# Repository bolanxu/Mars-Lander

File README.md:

# Mars Lander

https://youtu.be/TvxShnH4dns?si=FG6ILegN3fnswcwK

A Mars Lander control panel that simulates a landing on Mars. 
Built using simple physics, microcontrollers, and electronics.

This is is probably one of my most complex projects and it took me about a few months to build.
My first prototype was only a microcontroller development board with and 16x2 LCD screen (see /src/lcd)
And I made it in 7th grade, only about a year after I learned how to use the microcontroller.

I finish the 2nd upgraded prototype in December of 2024. I changed the LCD display to a full panel of 4 seven-segment displays, 8 leds, buttons, and potentiometers.
The code is in the /src/panel folder.

I used an microcontroller from the 8051 family, the STC125A60S2 developed by STC Microcontrollers. Compiled using SDCC.

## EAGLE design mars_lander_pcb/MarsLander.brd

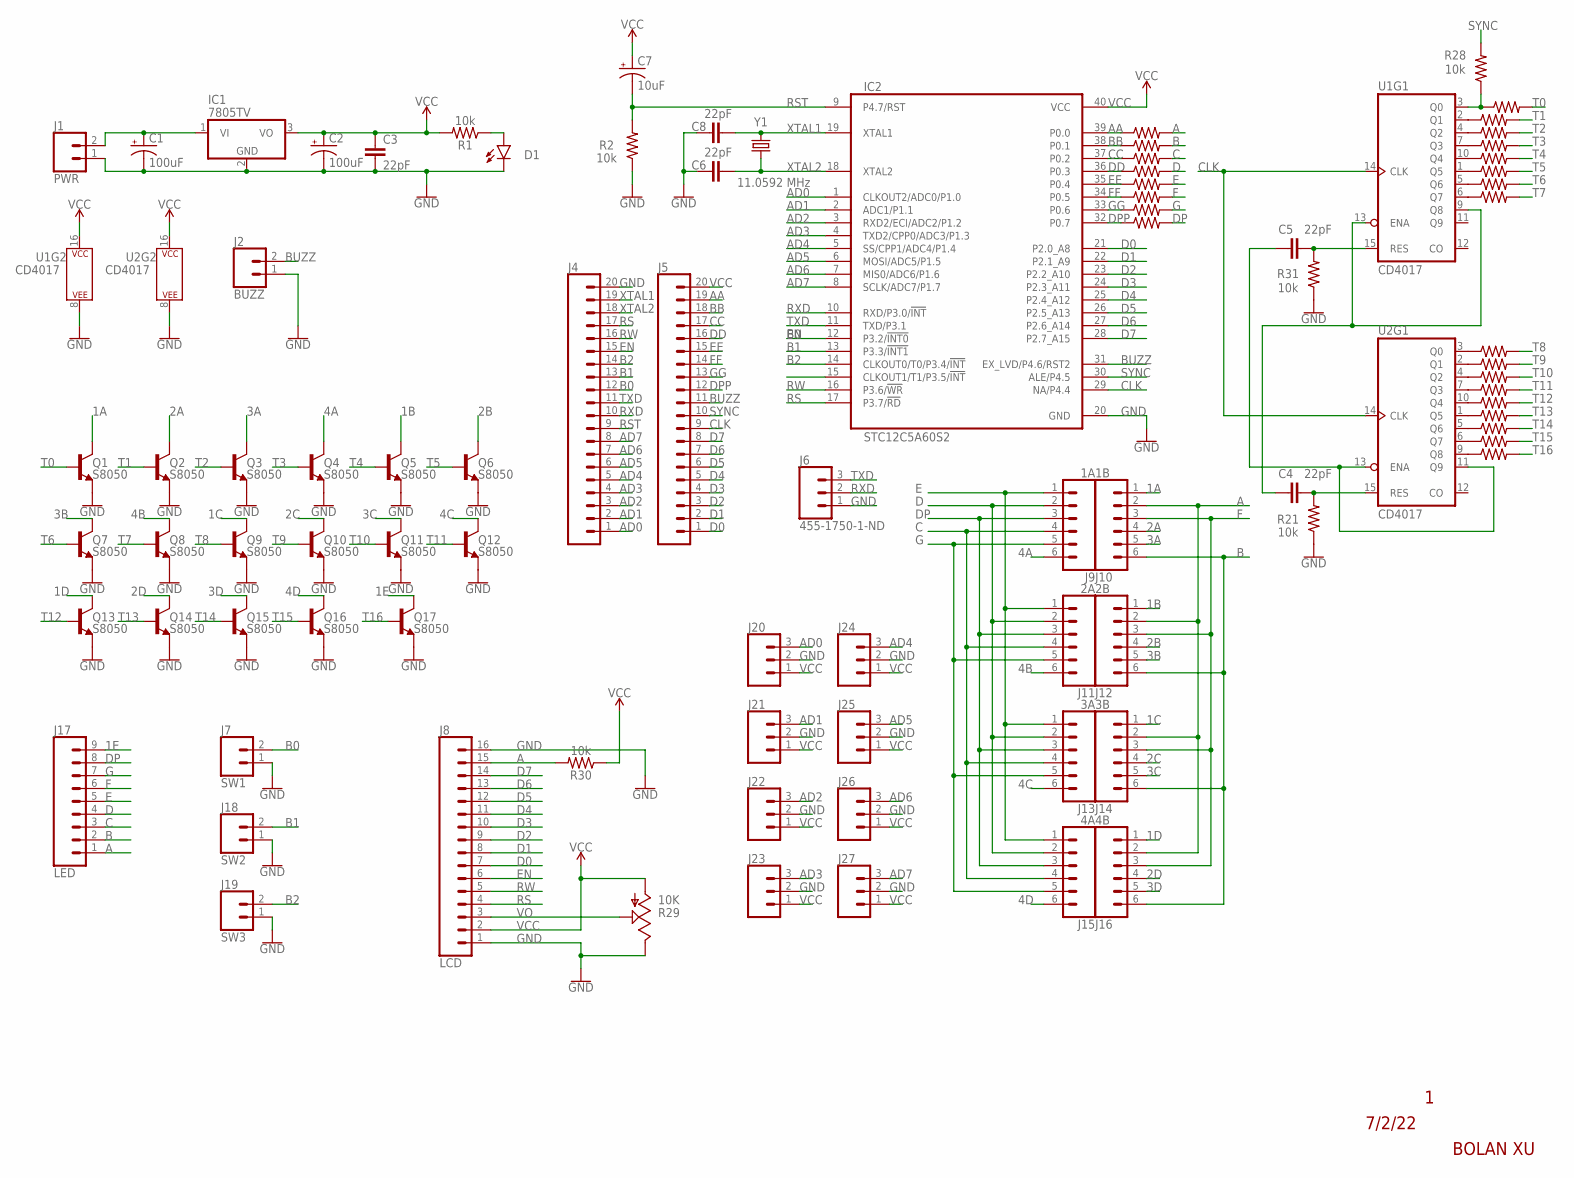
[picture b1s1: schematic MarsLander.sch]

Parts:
C1, C2: 100uF; CPOL-RADIAL-2.5MM-6.5MM
C3, C4, C5, C6, C8: 22pF; CAP-PTH-2.54
C7: 10uF; CPOL-RADIAL-2.5MM-5MM
D1: 3MM; LED_3MM
IC1: 7805TV; TO220V
IC2: STC12C5A60S2; DIL40
J1: PWR; 1X02
J2: BUZZ; 1X02
J4, J5: CONN_20; 1X20
J6, J20, J21, J22, J23, J24, J25, J26, J27: 455-1750-1-ND; 1X03
J7: SW1; 1X02
J8: LCD; 1X16
J9: 1A; 1X06
J10: 1B; 1X06
J11: 2A; 1X06
J12: 2B; 1X06
J13: 3A; 1X06
J14: 3B; 1X06
J15: 4A; 1X06
J16: 4B; 1X06
J17: LED; 1X09
J18: SW2; 1X02
J19: SW3; 1X02
Q1, Q2, Q3, Q4, Q5, Q6, Q7, Q8, Q9, Q10, Q11, Q12, Q13, Q14, Q15, Q16, Q17: S8050; TO-92
R1, R2, R3, R4, R5, R6, R7, R8, R9, R10, R11, R12, R13, R14, R15, R16, R17, R18, R19, R20, R21, R22, R23, R24, R25, R26, R27, R28, R30, R31, R33: 10k; AXIAL-0.3
R29: 10K; B25P
U1, U2: CD4017; DIP16
Y1: 11.0592 MHz; HC49U

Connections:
1A: J10.1, Q1.3 (C)
1B: J12.1, Q5.3 (C)
1C: J14.1, Q9.3 (C)
1D: J16.1, Q13.3 (C)
1E: J17.9, Q17.3 (C)
2A: J10.4, Q2.3 (C)
2B: J12.4, Q6.3 (C)
2C: J14.4, Q10.3 (C)
2D: J16.4, Q14.3 (C)
3A: J10.5, Q3.3 (C)
3B: J12.5, Q7.3 (C)
3C: J14.5, Q11.3 (C)
3D: J16.5, Q15.3 (C)
4A: J9.6, Q4.3 (C)
4B: J11.6, Q8.3 (C)
4C: J13.6, Q12.3 (C)
4D: J15.6, Q16.3 (C)
A: J8.15, J10.2, J12.2, J14.2, J16.2, J17.1, R19.P$2 (2), R30.P$2 (2)
AA: IC2.39 (P0.0), J5.19, R19.P$1 (1)
AD0: IC2.1 (CLKOUT2/ADC0/P1.0), J4.1, J20.3
AD1: IC2.2 (ADC1/P1.1), J4.2, J21.3
AD2: IC2.3 (RXD2/ECI/ADC2/P1.2), J4.3, J22.3
AD3: IC2.4 (TXD2/CPP0/ADC3/P1.3), J4.4, J23.3
AD4: IC2.5 (SS/CPP1/ADC4/P1.4), J4.5, J24.3
AD5: IC2.6 (MOSI/ADC5/P1.5), J4.6, J25.3
AD6: IC2.7 (MIS0/ADC6/P1.6), J4.7, J26.3
AD7: IC2.8 (SCLK/ADC7/P1.7), J4.8, J27.3
B: J10.6, J12.6, J14.6, J16.6, J17.2, R20.P$2 (2)
B0: IC2.12 (P3.2/!INT0), J4.12, J7.2
B1: IC2.13 (P3.3/!INT1), J4.13, J18.2
B2: IC2.14 (CLKOUT0/T0/P3.4/!INT), J4.14, J19.2
BB: IC2.38 (P0.1), J5.18, R20.P$1 (1)
BUZZ: IC2.31 (EX_LVD/P4.6/RST2), J2.2, J5.11
C: J9.4, J11.4, J13.4, J15.4, J17.3, R22.P$2 (2)
CC: IC2.37 (P0.2), J5.17, R22.P$1 (1)
CLK: IC2.29 (NA/P4.4), J5.9, U1.14 (CLK), U2.14 (CLK)
D: J9.2, J11.2, J13.2, J15.2, J17.4, R23.P$2 (2)
D0: IC2.21 (P2.0_A8), J5.1, J8.7
D1: IC2.22 (P2.1_A9), J5.2, J8.8
D2: IC2.23 (P2.2_A10), J5.3, J8.9
D3: IC2.24 (P2.3_A11), J5.4, J8.10
D4: IC2.25 (P2.4_A12), J5.5, J8.11
D5: IC2.26 (P2.5_A13), J5.6, J8.12
D6: IC2.27 (P2.6_A14), J5.7, J8.13
D7: IC2.28 (P2.7_A15), J5.8, J8.14
DD: IC2.36 (P0.3), J5.16, R23.P$1 (1)
DP: J9.3, J11.3, J13.3, J15.3, J17.8, R27.P$2 (2)
DPP: IC2.32 (P0.7), J5.12, R27.P$1 (1)
E: J9.1, J11.1, J13.1, J15.1, J17.5, R24.P$2 (2)
EE: IC2.35 (P0.4), J5.15, R24.P$1 (1)
EN: IC2.15 (CLKOUT1/T1/P3.5/!INT), J4.15, J8.6
F: J10.3, J12.3, J14.3, J16.3, J17.6, R25.P$2 (2)
FF: IC2.34 (P0.5), J5.14, R25.P$1 (1)
G: J9.5, J11.5, J13.5, J15.5, J17.7, R26.P$2 (2)
GG: IC2.33 (P0.6), J5.13, R26.P$1 (1)
GND: C1.2 (-), C2.2 (-), C3.2, C6.1, C8.1, D1.K (C), IC1.2 (GND), IC2.20 (GND), J1.1, J2.1, J4.20, J6.1, J7.1, J8.1, J8.16, J18.1, J19.1, J20.2, J21.2, J22.2, J23.2, J24.2, J25.2, J26.2, J27.2, Q1.1 (E), Q2.1 (E), Q3.1 (E), Q4.1 (E), Q5.1 (E), Q6.1 (E), Q7.1 (E), Q8.1 (E), Q9.1 (E), Q10.1 (E), Q11.1 (E), Q12.1 (E), Q13.1 (E), Q14.1 (E), Q15.1 (E), Q16.1 (E), Q17.1 (E), R2.P$1 (1), R21.P$1 (1), R29.E, R31.P$1 (1), U1.8 (P$V-), U2.8 (P$V-)
unnamed: C1.1 (+), IC1.1 (VI), J1.2
unnamed: C4.1, U1.9 (Q8), U1.13 (ENA)
unnamed: C5.1, U2.11 (Q9), U2.13 (ENA)
unnamed: C5.2, R31.P$2 (2), U1.15 (RES)
unnamed: C4.2, R21.P$2 (2), U2.15 (RES)
unnamed: R28.P$1 (1), R33.P$1 (1), U1.3 (Q0)
unnamed: R3.P$1 (1), U1.2 (Q1)
unnamed: R4.P$1 (1), U1.4 (Q2)
unnamed: R5.P$1 (1), U1.7 (Q3)
unnamed: R6.P$1 (1), U1.10 (Q4)
unnamed: R7.P$1 (1), U1.1 (Q5)
unnamed: R8.P$1 (1), U1.5 (Q6)
unnamed: R9.P$1 (1), U1.6 (Q7)
unnamed: R10.P$1 (1), U2.3 (Q0)
unnamed: R11.P$1 (1), U2.2 (Q1)
unnamed: R12.P$1 (1), U2.4 (Q2)
unnamed: D1.A, R1.P$1 (1)
unnamed: R13.P$1 (1), U2.7 (Q3)
unnamed: R14.P$1 (1), U2.10 (Q4)
unnamed: R15.P$1 (1), U2.1 (Q5)
unnamed: R16.P$1 (1), U2.5 (Q6)
unnamed: R17.P$1 (1), U2.6 (Q7)
unnamed: R18.P$1 (1), U2.9 (Q8)
RS: IC2.17 (P3.7/!RD), J4.17, J8.4
RST: C7.2 (-), IC2.9 (P4.7/RST), J4.9, R2.P$2 (2)
RW: IC2.16 (P3.6/!WR), J4.16, J8.5
RXD: IC2.10 (RXD/P3.0/!INT), J4.10, J6.2
SYNC: IC2.30 (ALE/P4.5), J5.10, R28.P$2 (2)
T0: Q1.2 (B), R33.P$2 (2)
T1: Q2.2 (B), R3.P$2 (2)
T2: Q3.2 (B), R4.P$2 (2)
T3: Q4.2 (B), R5.P$2 (2)
T4: Q5.2 (B), R6.P$2 (2)
T5: Q6.2 (B), R7.P$2 (2)
T6: Q7.2 (B), R8.P$2 (2)
T7: Q8.2 (B), R9.P$2 (2)
T8: Q9.2 (B), R10.P$2 (2)
T9: Q10.2 (B), R11.P$2 (2)
T10: Q11.2 (B), R12.P$2 (2)
T11: Q12.2 (B), R13.P$2 (2)
T12: Q13.2 (B), R14.P$2 (2)
T13: Q14.2 (B), R15.P$2 (2)
T14: Q15.2 (B), R16.P$2 (2)
T15: Q16.2 (B), R17.P$2 (2)
T16: Q17.2 (B), R18.P$2 (2)
TXD: IC2.11 (TXD/P3.1), J4.11, J6.3
VCC: C2.1 (+), C3.1, C7.1 (+), IC1.3 (VO), IC2.40 (VCC), J5.20, J8.2, J20.1, J21.1, J22.1, J23.1, J24.1, J25.1, J26.1, J27.1, R1.P$2 (2), R29.A, R30.P$1 (1), U1.16 (P$V+), U2.16 (P$V+)
VO: J8.3, R29.S
XTAL1: C8.2, IC2.19 (XTAL1), J4.19, Y1.2
XTAL2: C6.2, IC2.18 (XTAL2), J4.18, Y1.1

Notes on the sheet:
BOLAN XU
7/2/22

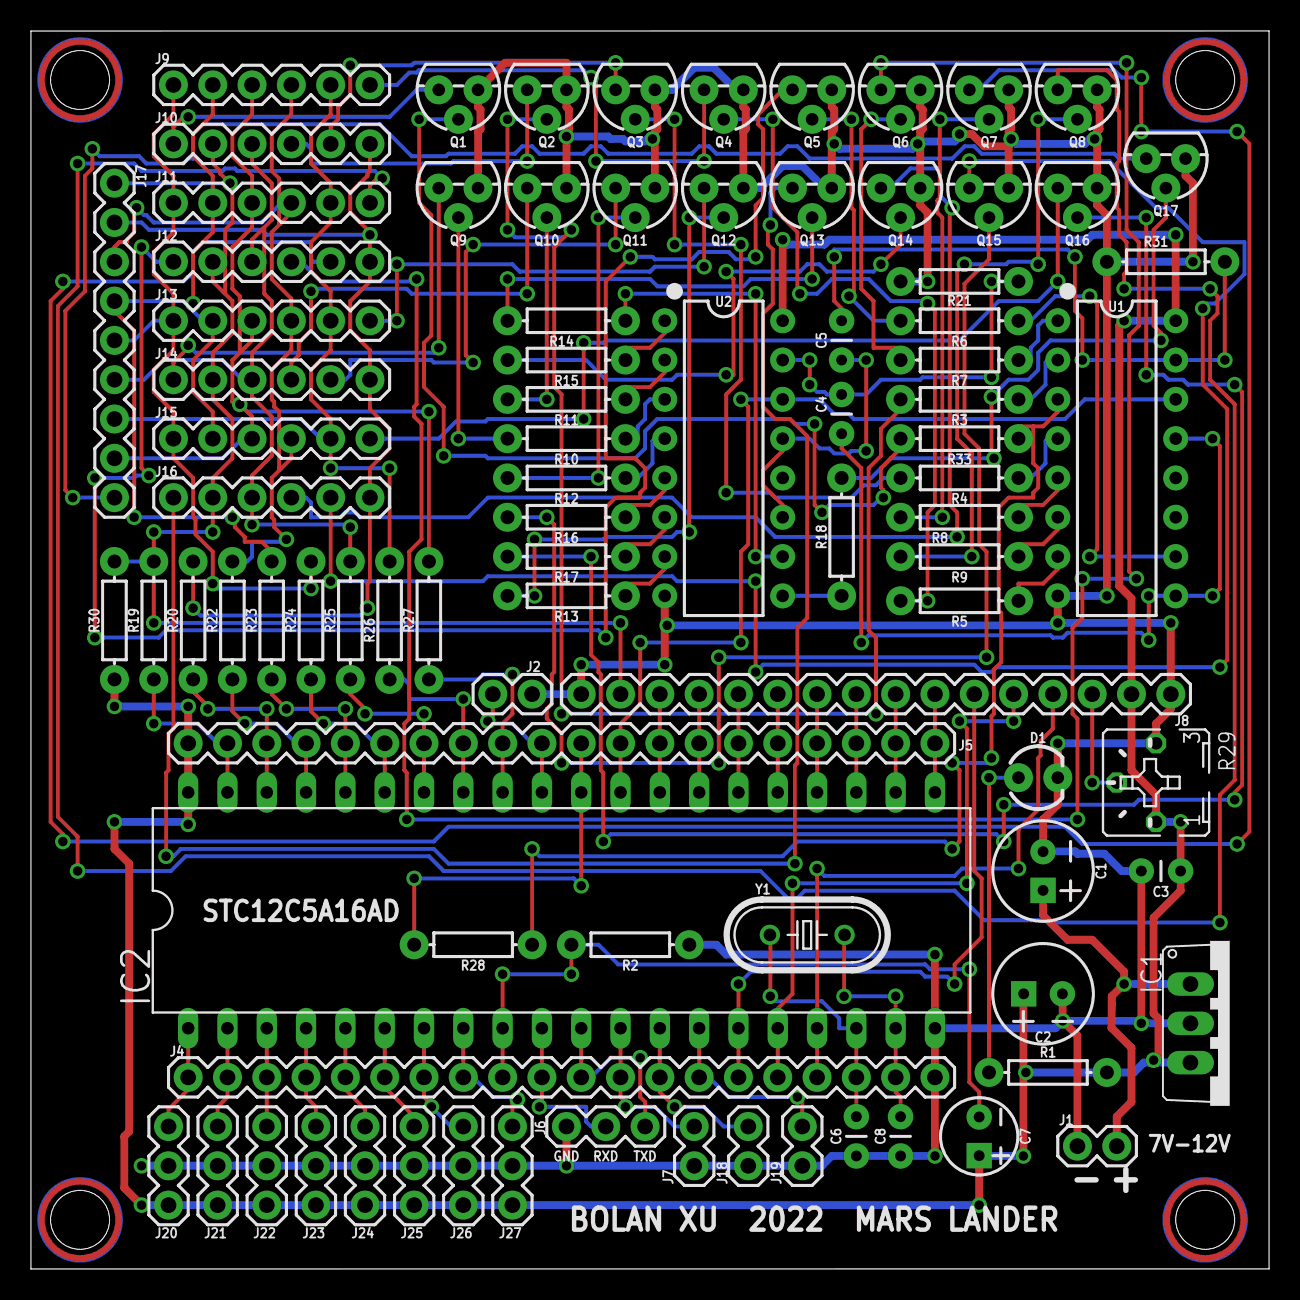
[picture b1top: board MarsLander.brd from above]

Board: 2 copper layers, 80.0 x 80.0 mm, 89 parts (0 on the bottom side), 106 nets.

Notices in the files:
parts and their libraries:
SparkFun-Capacitors: Licensing: Creative Commons ShareAlike 4.0 International - https://creativecommons.org/licenses/by-sa/4.0
